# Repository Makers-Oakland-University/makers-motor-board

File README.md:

# Makers @ OU General Purpose Motor Board

The Makers @ OU motor board is meant to serve as a general-purpose robot base for all kinds of projects. 
The board utilizes the ESP32 Devkit 1, along with an L293D H-Bridge driver. 
The LM7805 voltage regulator enables the board to be powered from any supply between 4.5V and 30V. 
The input voltage can be used directly to drive the motor, or the 5V power rail can be used through selection through the header. 

This repo contains the KiCad EDA files for the board, gerber production files, the board schematic in PDF format, and a .step file to aid CAD design. 

# ESP32 Pin Connections

The following pins on the ESP32 are connected to the motor driver:

- IO26 -> Driver 1A
- IO27 -> Driver 2A
- IO23 -> Driver 3A
- IO25 -> Driver 4A
- IO32 -> Driver 1,2EN
- IO33 -> Driver 3,4EN

# BOM 
This section provides a list of components used by this board, and some amazon links that can be used to acquire them. 

- [ESP32 DevKit V1](https://www.amazon.com/ESP32-WROOM-32-Development-ESP-32S-Bluetooth-Arduino/dp/B084KWNMM4/ref=sr_1_1_sspa?crid=8881ZROOTJFK&keywords=ESP32+devkit&qid=1674351980&sprefix=esp32+devkit+%2Caps%2C108&sr=8-1-spons&psc=1&spLa=ZW5jcnlwdGVkUXVhbGlmaWVyPUExU0RPNzlPNUpQTTFUJmVuY3J5cHRlZElkPUEwMzA4OTc1M080TFlWOFMxVkRGUiZlbmNyeXB0ZWRBZElkPUEwOTA5NTc0MTdUSDJMWDFHTEU4RyZ3aWRnZXROYW1lPXNwX2F0ZiZhY3Rpb249Y2xpY2tSZWRpcmVjdCZkb05vdExvZ0NsaWNrPXRydWU=)
- [L293D Motor Driver](https://www.amazon.com/BOJACK-16-pin-Stepper-Drivers-Controllers/dp/B09NBQVYLL/ref=sr_1_1_sspa?crid=2IHZB0VAWDBTZ&keywords=L293D&qid=1674351391&sprefix=l293d%2Caps%2C357&sr=8-1-spons&psc=1&spLa=ZW5jcnlwdGVkUXVhbGlmaWVyPUExWFlUOFpBSUhMSkY4JmVuY3J5cHRlZElkPUEwNzEwMTg5MUdVTDAzMVlWUzZSTyZlbmNyeXB0ZWRBZElkPUEwNjY0MzQxUFQwMkg5TFZHT0hWJndpZGdldE5hbWU9c3BfYXRmJmFjdGlvbj1jbGlja1JlZGlyZWN0JmRvTm90TG9nQ2xpY2s9dHJ1ZQ==)
- [LM7805 Voltage Regulator](https://www.amazon.com/BOJACK-Regulator-Integrated-Circuits-Regulators/dp/B07VRS9HW4/ref=sr_1_2_sspa?crid=114WNR497M2D3&keywords=LM7805&qid=1674351959&sprefix=lm7805%2Caps%2C107&sr=8-2-spons&psc=1&spLa=ZW5jcnlwdGVkUXVhbGlmaWVyPUEzSTFNWldGTEYyM1ZHJmVuY3J5cHRlZElkPUEwNjMwMzEyM002TFE5SFA0UUI3MyZlbmNyeXB0ZWRBZElkPUEwMTMyMDg5MktBWFBDWjVRTEJRWiZ3aWRnZXROYW1lPXNwX2F0ZiZhY3Rpb249Y2xpY2tSZWRpcmVjdCZkb05vdExvZ0NsaWNrPXRydWU=)
- [2 Position 5mm Pitch Terminal Blocks](https://www.amazon.com/DIYhz-green-Terminal-Connector-Arduino/dp/B0774YRVVX/ref=sr_1_16?crid=2E3RW9V76RSA4&keywords=5mm+2+position+terminals&qid=1674352018&sprefix=5mm+2+positio+terminals%2Caps%2C109&sr=8-16)
- [Standard Header Jumpers (only need 1 per board)](https://www.amazon.com/uxcell-100pcs-Standard-Circuit-Connection/dp/B08Y7Y9LKV/ref=sr_1_4?crid=TVEIYRUGLAMC&keywords=header+jumpers&qid=1674352070&sprefix=header+jumper%2Caps%2C107&sr=8-4)

Any electrolytic capacitor can be used provided it's voltage rating is above the input voltage present at PWR IN

# Acknoledgements 
This repo uses Victor Lamoine's [ESP32 Devkit V1 Symbol and Footprint](https://gitlab.com/VictorLamoine/kicad).

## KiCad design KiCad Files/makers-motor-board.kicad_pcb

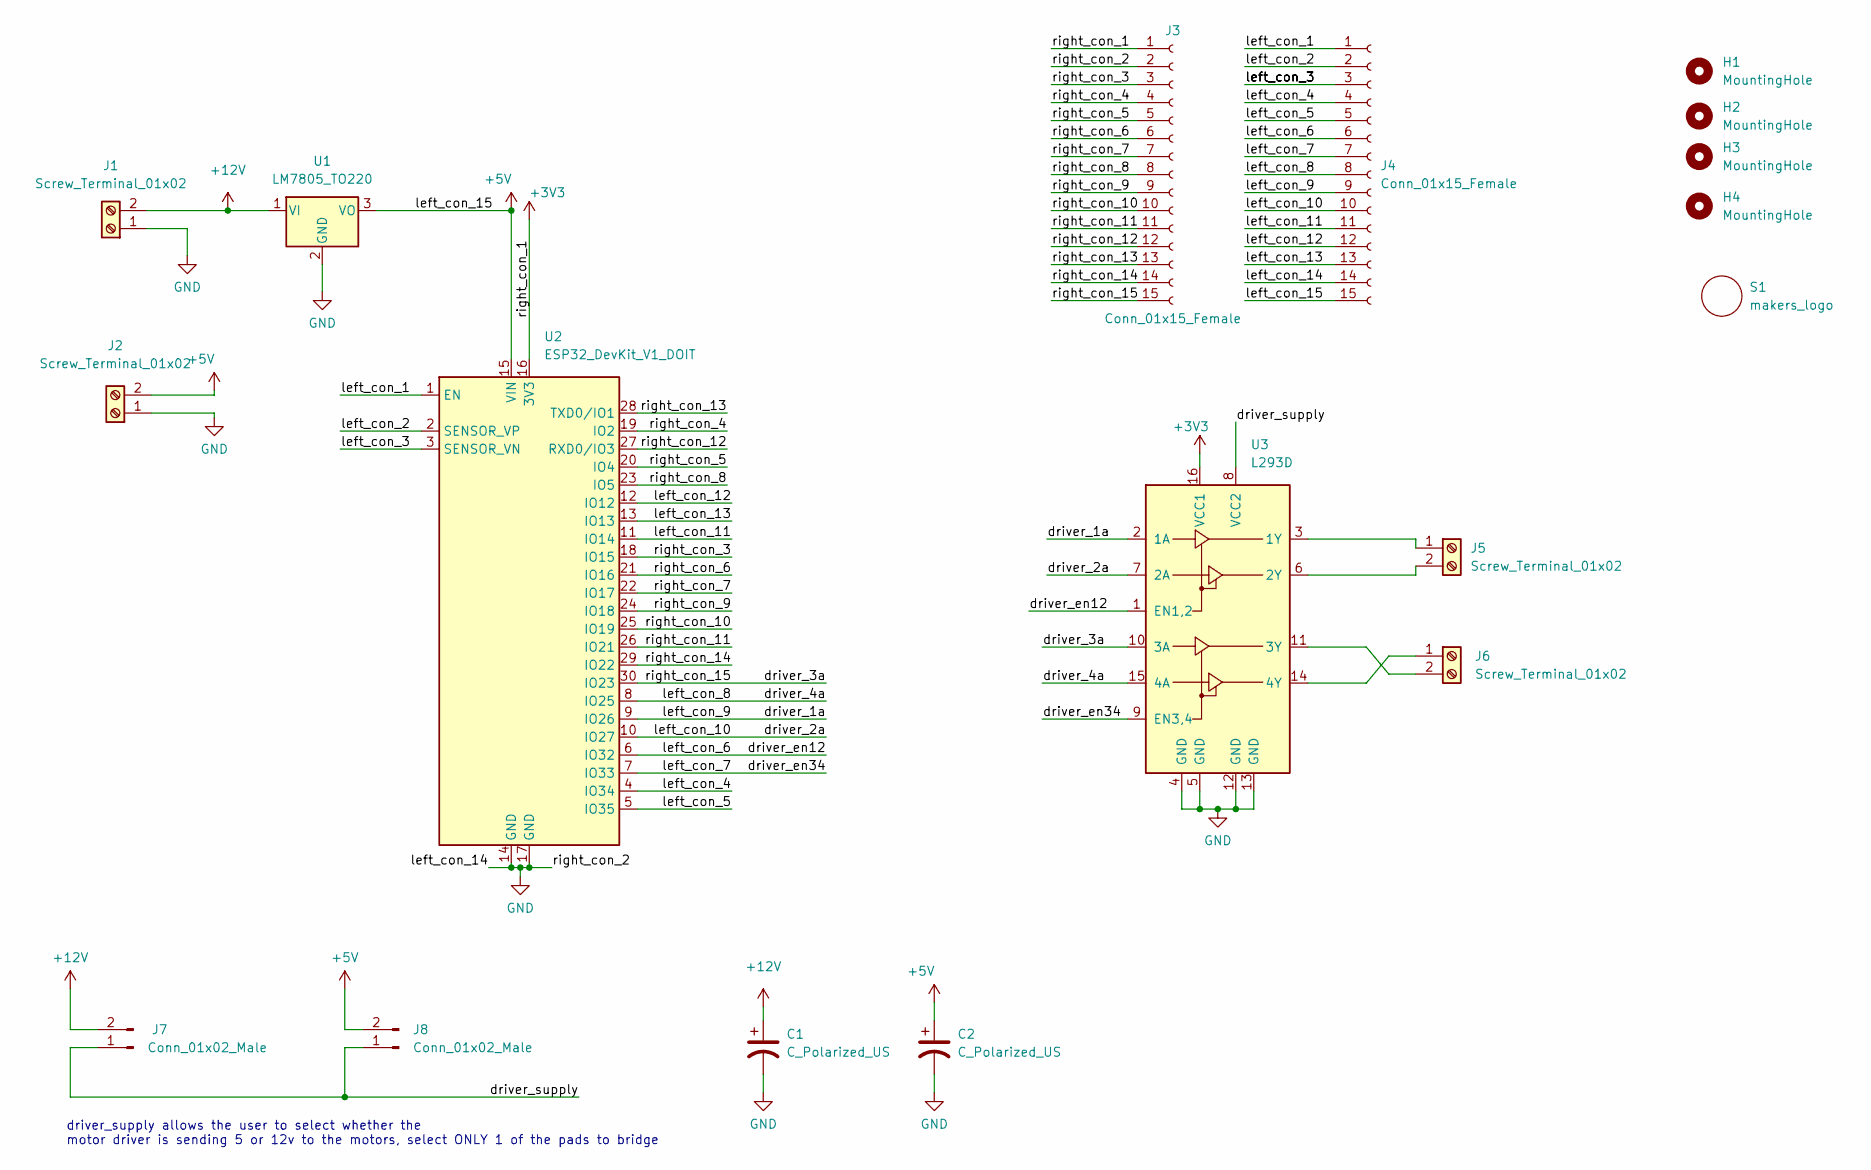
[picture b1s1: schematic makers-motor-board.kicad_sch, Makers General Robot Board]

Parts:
C1, C2: C_Polarized_US; CP_Radial_D8.0mm_P3.50mm
H1, H2, H3, H4: MountingHole; MountingHole_3.2mm_M3_Pad
J1, J2, J5, J6: Screw_Terminal_01x02; terminal_block_5mm
J3, J4: Conn_01x15_Female; PinSocket_1x15_P2.54mm_Vertical
J7, J8: Conn_01x02_Male; PinHeader_1x02_P2.54mm_Vertical
S1: makers_logo
U1: LM7805_TO220; TO-220-3_Horizontal_TabDown
U2: ESP32_DevKit_V1_DOIT; esp32_devkit_v1_doit
U3: L293D; DIP-16_W7.62mm

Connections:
+3V3: J3.1, U2.16 (3V3), U3.16 (VCC1)
+5V: C2.1, J2.2, J4.15, J8.2, U1.3 (VO), U2.15 (VIN)
+12V: C1.1, J1.2, J7.2, U1.1 (VI)
/driver_1a: J4.9, U2.9 (IO26), U3.2 (1A)
/driver_2a: J4.10, U2.10 (IO27), U3.7 (2A)
/driver_3a: J3.15, U2.30 (IO23), U3.10 (3A)
/driver_4a: J4.8, U2.8 (IO25), U3.15 (4A)
/driver_en12: J4.6, U2.6 (IO32), U3.1 (EN1,2)
/driver_en34: J4.7, U2.7 (IO33), U3.9 (EN3,4)
/driver_supply: J7.1, J8.1, U3.8 (VCC2)
/left_con_1: J4.1, U2.1 (EN)
/left_con_2: J4.2, U2.2 (SENSOR_VP)
/left_con_3: J4.3, U2.3 (SENSOR_VN)
/left_con_4: J4.4, U2.4 (IO34)
/left_con_5: J4.5, U2.5 (IO35)
/left_con_11: J4.11, U2.11 (IO14)
/left_con_12: J4.12, U2.12 (IO12)
/left_con_13: J4.13, U2.13 (IO13)
/right_con_3: J3.3, U2.18 (IO15)
/right_con_4: J3.4, U2.19 (IO2)
/right_con_5: J3.5, U2.20 (IO4)
/right_con_6: J3.6, U2.21 (IO16)
/right_con_7: J3.7, U2.22 (IO17)
/right_con_8: J3.8, U2.23 (IO5)
/right_con_9: J3.9, U2.24 (IO18)
/right_con_10: J3.10, U2.25 (IO19)
/right_con_11: J3.11, U2.26 (IO21)
/right_con_12: J3.12, U2.27 (RXD0/IO3)
/right_con_13: J3.13, U2.28 (TXD0/IO1)
/right_con_14: J3.14, U2.29 (IO22)
GND: C1.2, C2.2, J1.1, J2.1, J3.2, J4.14, U1.2 (GND), U2.14 (GND), U2.17 (GND), U3.4 (GND), U3.5 (GND), U3.12 (GND), U3.13 (GND)
unnamed: J5.1, U3.3 (1Y)
unnamed: J5.2, U3.6 (2Y)
unnamed: J6.1, U3.14 (4Y)
unnamed: J6.2, U3.11 (3Y)

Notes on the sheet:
driver_supply allows the user to select whether the motor driver is sending 5 or 12v to the motors, select ONLY 1 of the pads to bridge

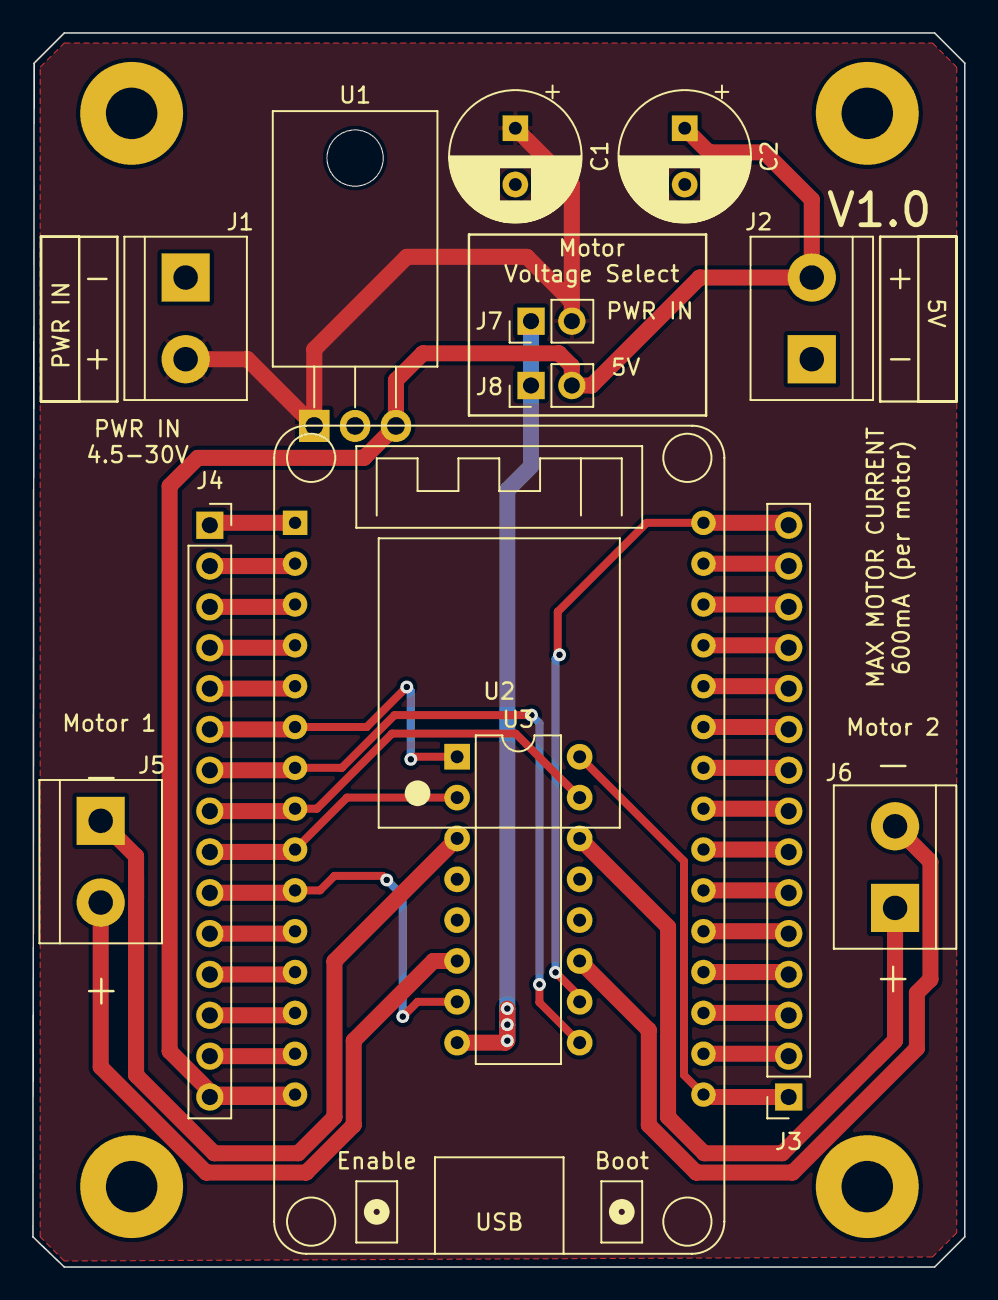
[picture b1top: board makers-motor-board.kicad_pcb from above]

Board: 2 copper layers, 58.0 x 76.8 mm, 18 parts (1 on the bottom side), 35 nets.

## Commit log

2023-01-22 Commit of Version 1 of the Makers Motor Board
